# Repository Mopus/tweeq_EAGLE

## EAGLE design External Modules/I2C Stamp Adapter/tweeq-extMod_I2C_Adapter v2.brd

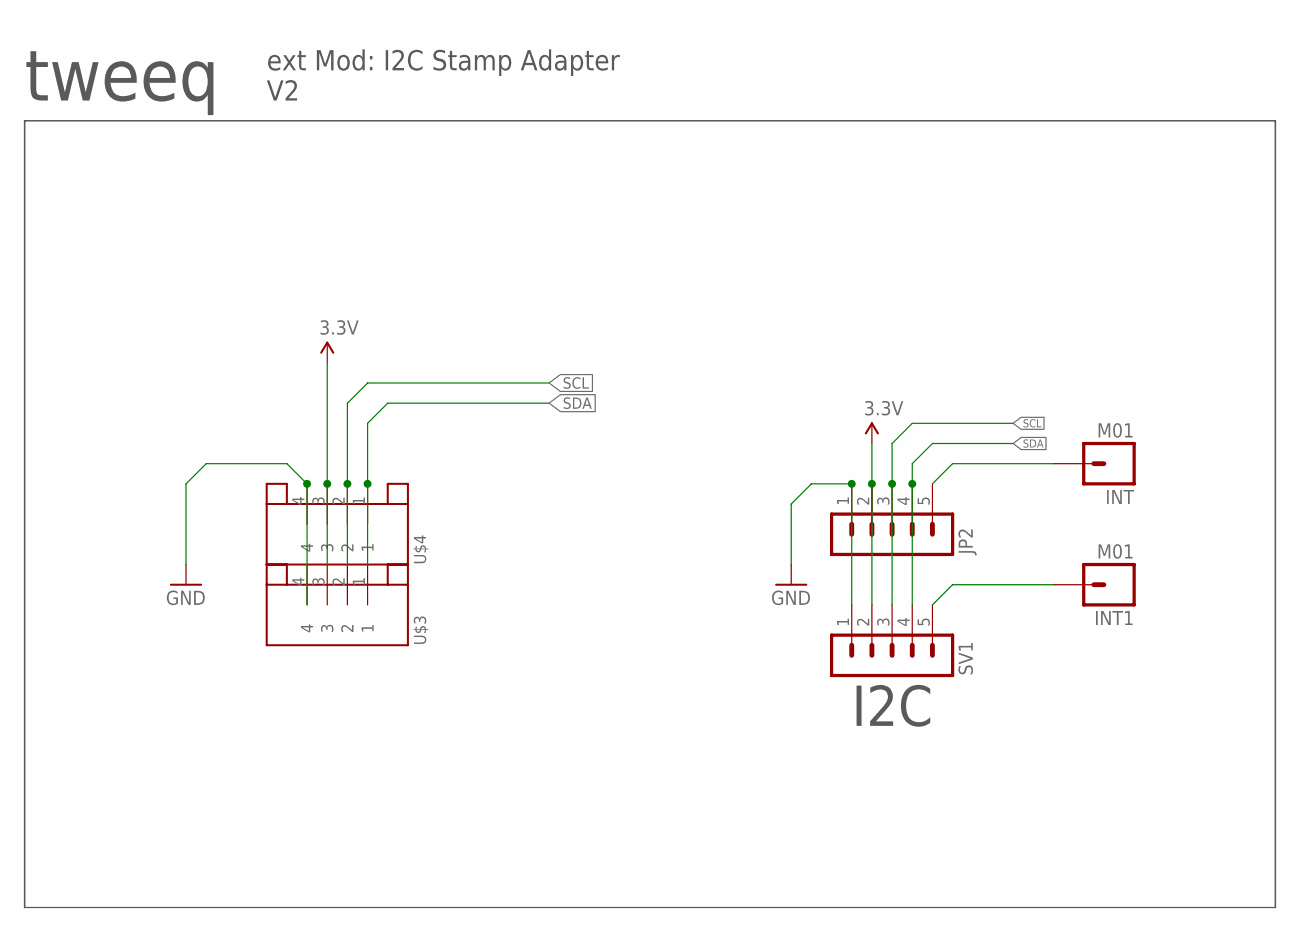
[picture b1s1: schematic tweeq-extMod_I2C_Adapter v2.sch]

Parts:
INT, INT1: M01; AISCUBE_1X01_TIGHTFITVIA
JP2: M05-11.5MM-SMT; 1X05-1.5MM-SMT
SV1: M05-11.5MM-SMT; 1X05-1.5MM-SMT
U$3, U$4: JST-4PINSH; SH1.0-4PIN

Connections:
3.3V: JP2.2, SV1.2, U$3.3, U$4.3
GND: JP2.1, SV1.1, U$4.4
INT: INT.P$1, JP2.5
unnamed: INT1.P$1, SV1.5
SCL: JP2.3, SV1.3, U$3.2, U$4.2
SDA: JP2.4, SV1.4, U$3.1, U$4.1

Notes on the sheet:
tweeq
ext Mod: I2C Stamp Adapter V2
I2C

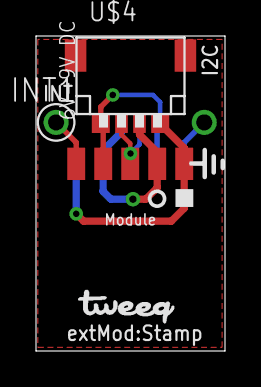
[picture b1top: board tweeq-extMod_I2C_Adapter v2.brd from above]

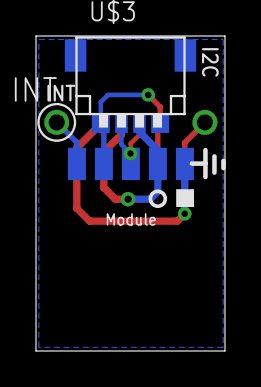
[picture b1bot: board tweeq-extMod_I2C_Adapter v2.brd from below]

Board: 2 copper layers, 10.5 x 17.5 mm, 7 parts (3 on the bottom side), 6 nets.

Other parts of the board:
U$1: TWEEQ-LOGO-S

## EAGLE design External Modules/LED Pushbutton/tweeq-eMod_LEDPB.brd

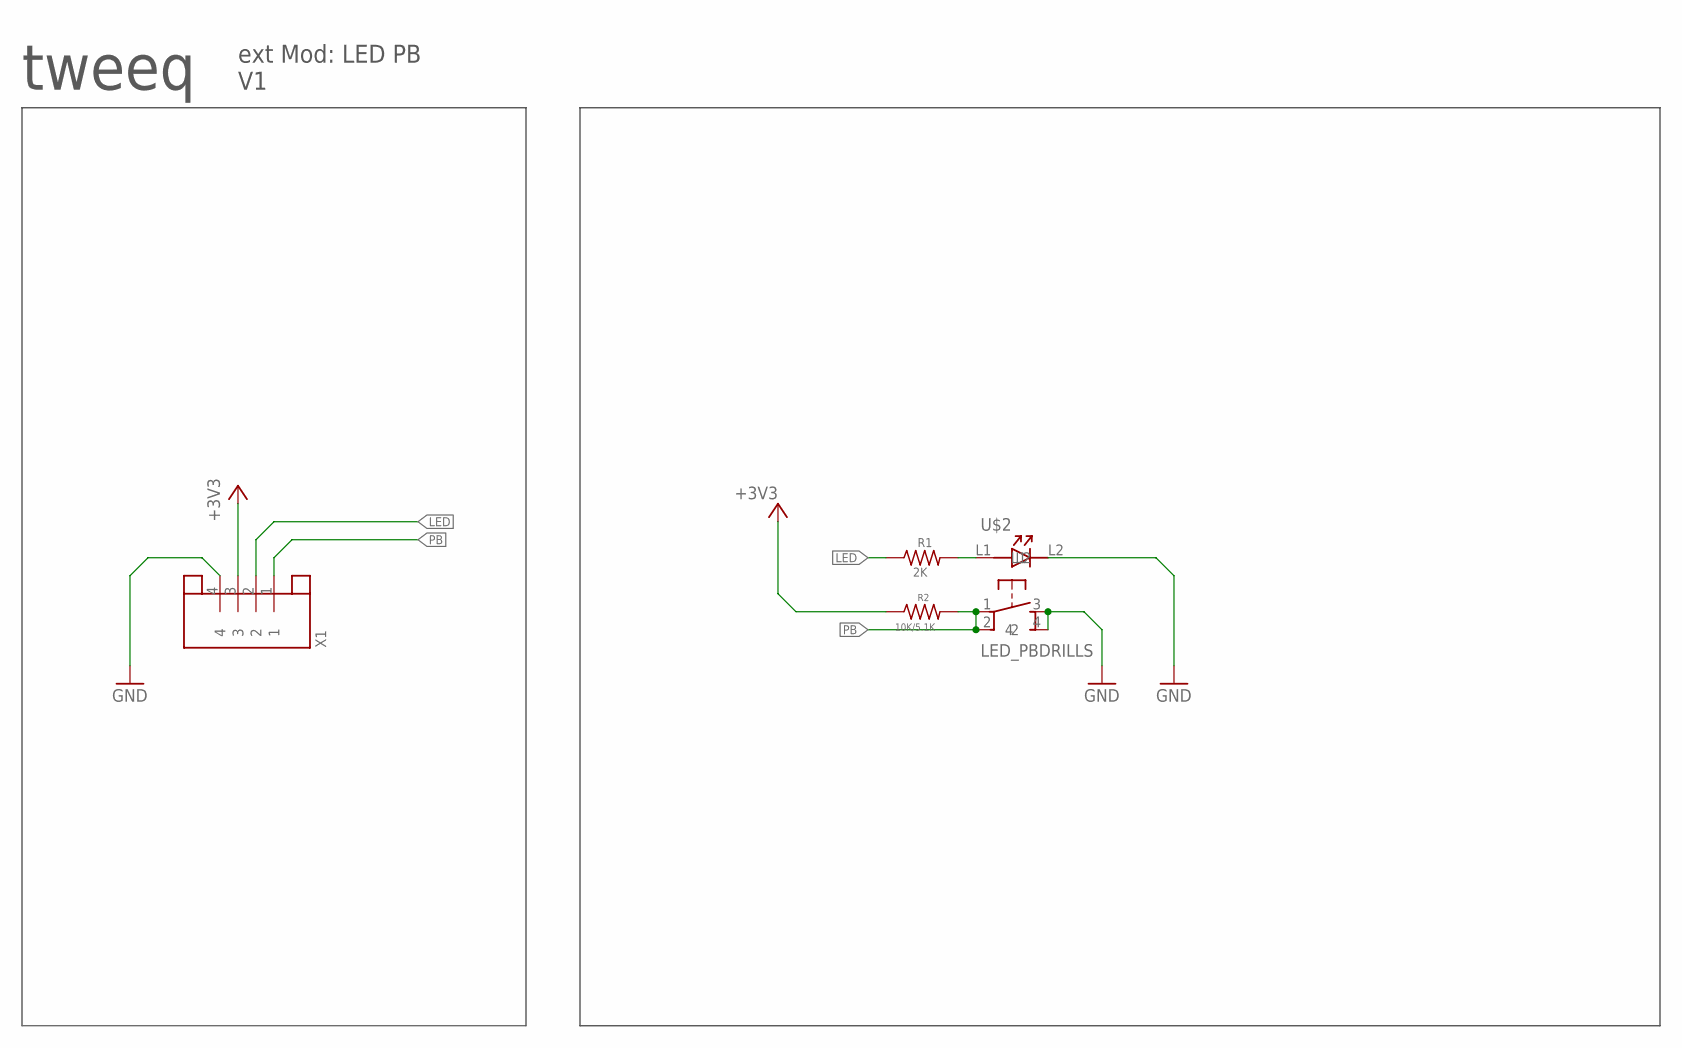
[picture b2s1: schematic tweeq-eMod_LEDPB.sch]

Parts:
R1: 2K; R0603
R2: 10K/5.1K; R0603
U$2: LED_PBDRILLS; LED_PB_12X12_SMD_HOLES
X1: JST-4PINSH; SH1.0-4PIN

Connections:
+3V3: R2.1, X1.3
GND: U$2.3, U$2.4, U$2.L2, X1.4
LED: R1.1, X1.2
unnamed: R1.2, U$2.L1
PB: R2.2, U$2.1, U$2.2, X1.1

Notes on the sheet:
tweeq
ext Mod: LED PB V1

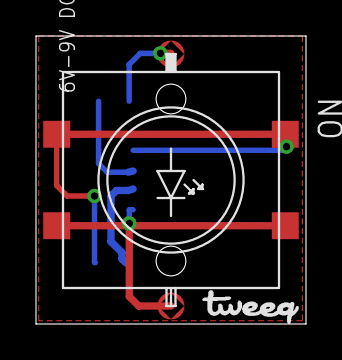
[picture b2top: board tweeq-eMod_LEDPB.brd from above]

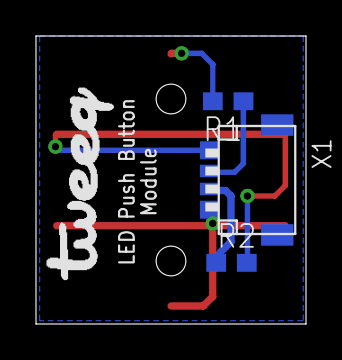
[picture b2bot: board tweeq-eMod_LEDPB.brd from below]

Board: 2 copper layers, 15.0 x 16.0 mm, 6 parts (4 on the bottom side), 5 nets.

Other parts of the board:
U$4: TWEEQ-LOGO-S
U$5: TWEEQ-LOGO-L

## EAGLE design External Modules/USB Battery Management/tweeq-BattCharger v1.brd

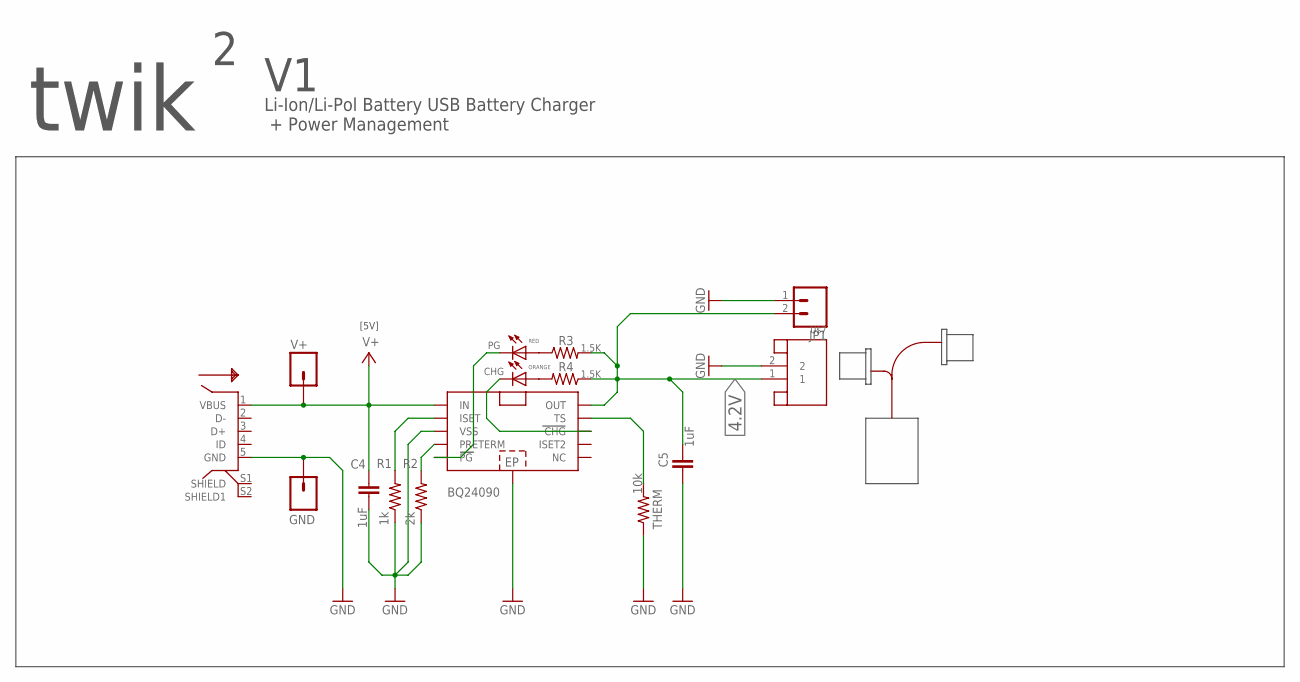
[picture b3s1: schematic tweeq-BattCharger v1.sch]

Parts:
BQ24090: BQ2409X-DGQ; MSOP10_POWERPAD
C4, C5: 1uF; C0603K
CHG: ORANGE; CHIP-LED0603
GND: M01SQ_NS; 1X01_SQ
JP1: M022.54-POL-TH; 1X02_2.54POL_TH
PG: RED; CHIP-LED0603
R1: 1k; R0402
R2: 2k; R0402
R3, R4: 1.5K; R0402
THERM: 10k; R0402
U$2: USB/MICRO-5PF-B; MICRO_USB_5PF_B
U$7: JST-2PINSH; SH1.0-2PIN
V+: M01/R_NS; 1X01NS

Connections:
4.2V: BQ24090.10 (OUT), C5.2, JP1.2, R3.2, R4.1, U$7.1
GND: BQ24090.3 (VSS), BQ24090.EP, C4.2, C5.1, GND.1, JP1.1, R1.1, R2.1, THERM.1, U$2.5 (GND), U$7.2
unnamed: BQ24090.2 (ISET), R1.2
unnamed: BQ24090.5 (PG), PG.C
unnamed: BQ24090.4 (PRETERM), R2.2
unnamed: PG.A, R3.1
unnamed: BQ24090.9 (TS), THERM.2
unnamed: BQ24090.8 (CHG), CHG.C
unnamed: CHG.A, R4.2
V+: BQ24090.1 (IN), C4.1, U$2.1 (VBUS), V+.1

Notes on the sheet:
[5V]
twik
Li-Ion/Li-Pol Battery USB Battery Charger + Power Management

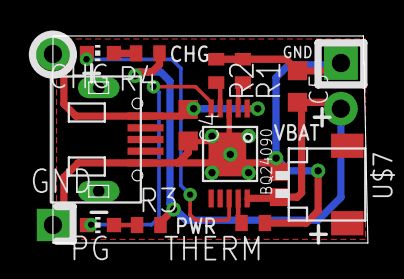
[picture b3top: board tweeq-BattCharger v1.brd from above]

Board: 2 copper layers, 17.5 x 11.5 mm, 16 parts (1 on the bottom side), 10 nets.

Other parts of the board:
U$1: TWEEQ-LOGO-M

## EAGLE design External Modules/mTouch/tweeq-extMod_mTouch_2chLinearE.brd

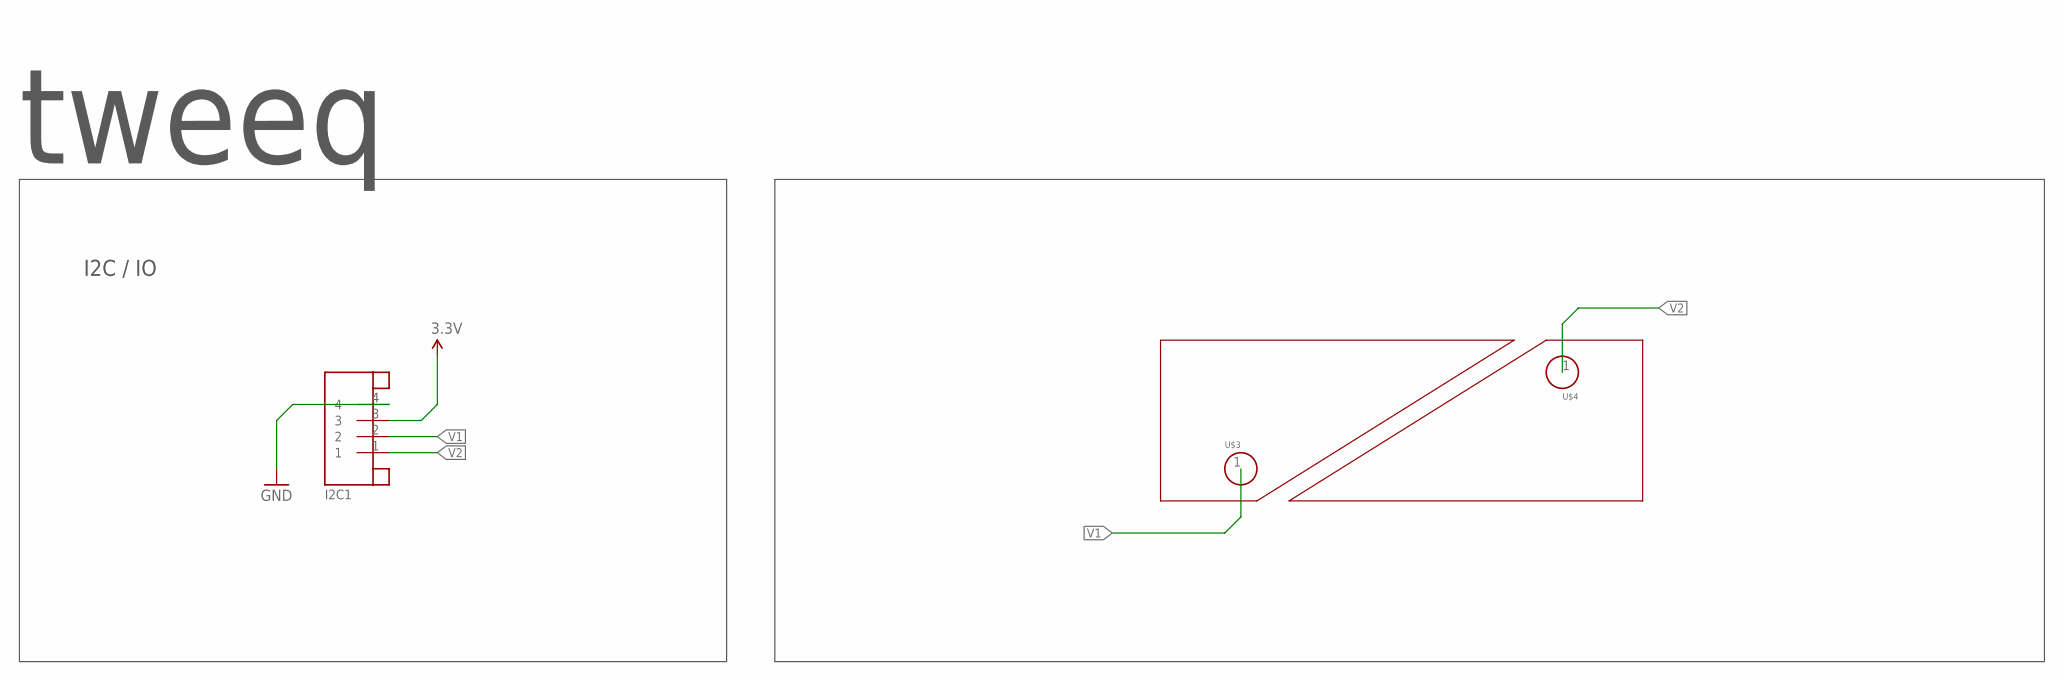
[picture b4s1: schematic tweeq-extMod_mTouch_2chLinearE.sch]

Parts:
I2C1: JST-4PINSH; SH1.0-4PIN
U$3, U$4: MTOUCH_VIA

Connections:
3.3V: I2C1.3
GND: I2C1.4
V1: I2C1.2, U$3.1
V2: I2C1.1, U$4.1

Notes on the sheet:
tweeq
I2C / IO

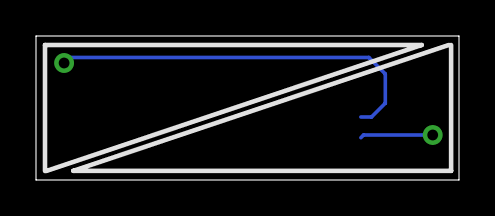
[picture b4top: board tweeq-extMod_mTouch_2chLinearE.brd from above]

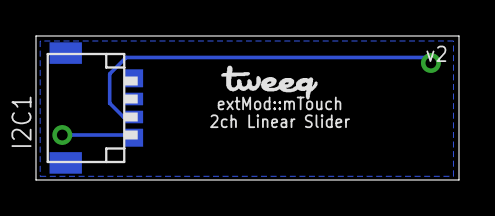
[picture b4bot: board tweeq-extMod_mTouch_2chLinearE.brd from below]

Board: 2 copper layers, 23.5 x 8.0 mm, 4 parts (2 on the bottom side), 2 nets.

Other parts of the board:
U$1: TWEEQ-LOGO-S

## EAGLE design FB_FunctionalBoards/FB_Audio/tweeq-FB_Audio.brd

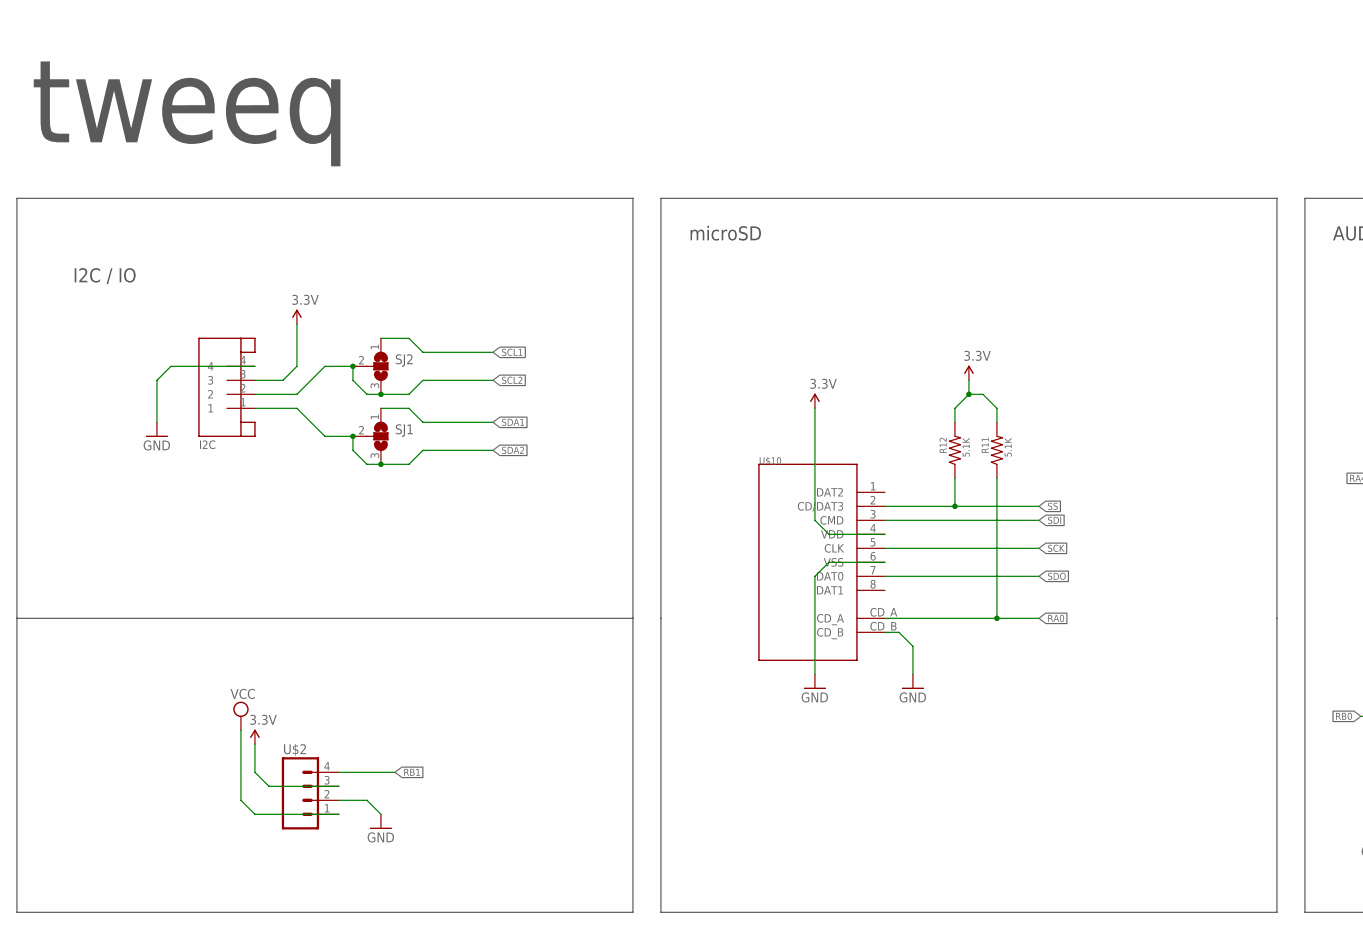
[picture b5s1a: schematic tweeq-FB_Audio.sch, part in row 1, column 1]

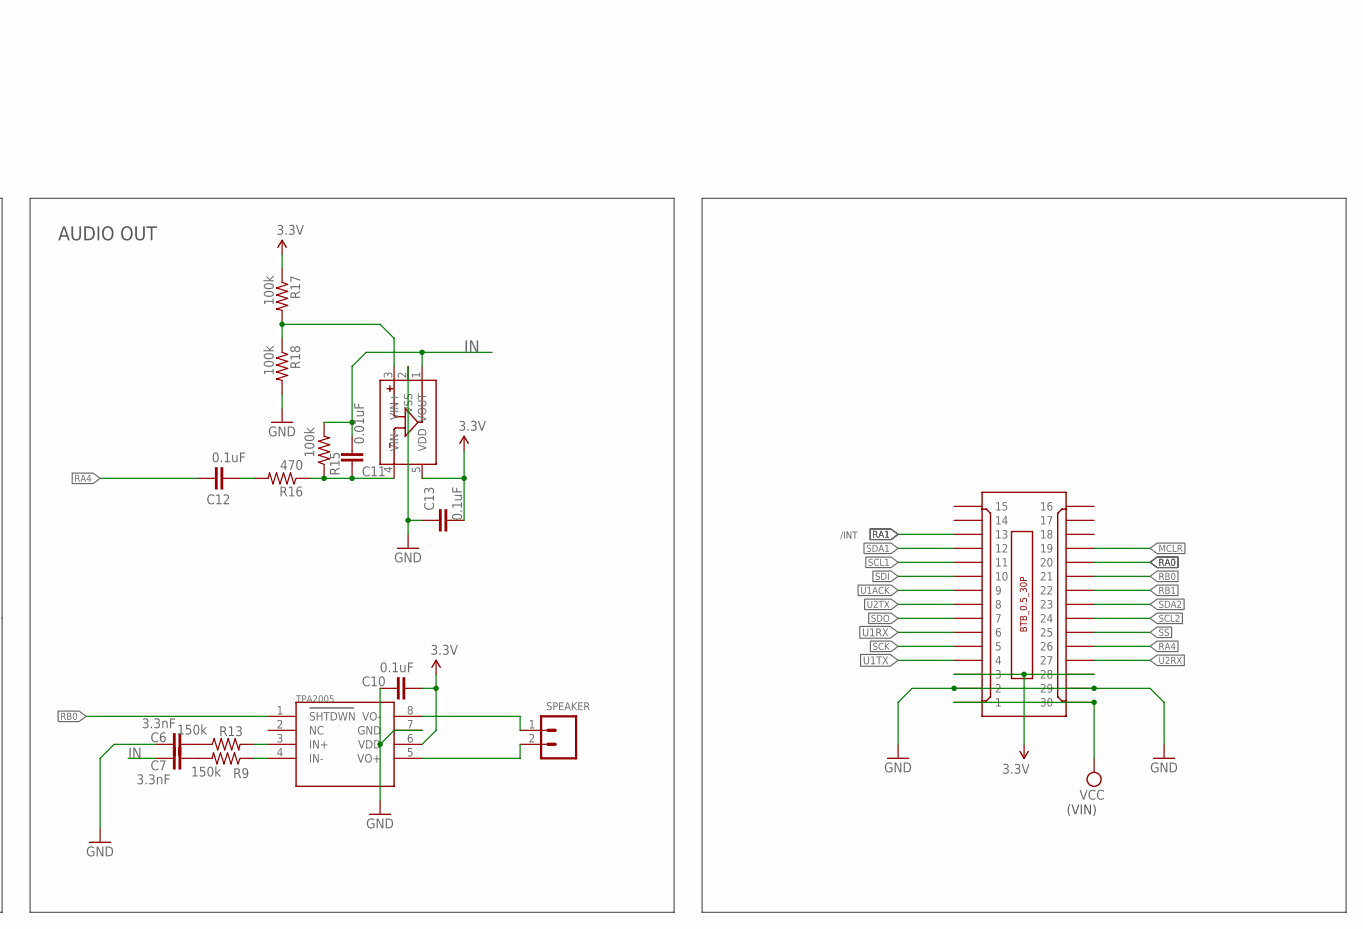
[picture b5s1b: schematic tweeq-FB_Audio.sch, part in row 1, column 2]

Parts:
C6, C7: 3.3nF; C0402
C10, C12, C13: 0.1uF; C0402
C11: 0.01uF; C0402
I2C: JST-4PINSH; SH1.0-4PIN
MCP6001/OT: MCP6001/OT; SOT23-5
R9, R13: 150k; R0402
R11, R12: 5.1K; R0402
R15, R17, R18: 100k; R0402
R16: 470; 0402-RES
SJ1, SJ2: JUMPER_SJ2WS; JUMPER_SJ_S
SPEAKER: LOUDSPEAKER; 1X02
TPA2005: TPA2005; MSOP8
U$1: BTB_CONN_30P/F; BTB0.5-30F-3.0G
U$2: M04; 1X04_PAD
U$10: MICROSD_DM3D; DM3D-SF

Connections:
3.3V: C10.2, C13.2, I2C.3, MCP6001/OT.5 (VDD), R11.2, R12.2, R17.1, TPA2005.6 (VDD), U$1.3, U$1.28, U$2.3, U$10.4 (VDD)
GND: C6.1, C10.1, C13.1, I2C.4, MCP6001/OT.2 (VSS), R18.2, TPA2005.7 (GND), U$1.2, U$1.29, U$2.2, U$10.6 (VSS), U$10.CD_B
IN: C7.2, C11.2, MCP6001/OT.1 (VOUT), R15.2
MCLR: U$1.19
unnamed: R9.1, TPA2005.4 (IN-)
unnamed: C7.1, R9.2
unnamed: R13.2, TPA2005.3 (IN+)
unnamed: C6.2, R13.1
unnamed: SPEAKER.1, TPA2005.8 (VO-)
unnamed: SPEAKER.2, TPA2005.5 (VO+)
unnamed: C12.2, R16.2
unnamed: C11.1, MCP6001/OT.4 (VIN-), R15.1, R16.1
unnamed: MCP6001/OT.3 (VIN+), R17.2, R18.1
RA0: R11.1, U$1.20, U$10.CD_A
RA1: U$1.13
RA4: C12.1, U$1.26
RB0: TPA2005.1 (SHTDWN), U$1.21
RB1: U$1.22, U$2.4
SCK: U$1.5, U$10.5 (CLK)
SCL1: SJ2.1, U$1.11
SCL2: I2C.2, SJ2.2, SJ2.3, U$1.24
SDA1: SJ1.1, U$1.12
SDA2: I2C.1, SJ1.2, SJ1.3, U$1.23
SDI: U$1.10, U$10.3 (CMD)
SDO: U$1.7, U$10.7 (DAT0)
SS: R12.1, U$1.25, U$10.2 (CD/DAT3)
U1ACK: U$1.9
U1RX: U$1.6
U1TX: U$1.4
U2RX: U$1.27
U2TX: U$1.8
VCC: U$1.1, U$1.30, U$2.1

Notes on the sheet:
AUDIO OUT
(VIN)
tweeq
microSD
I2C / IO
/INT

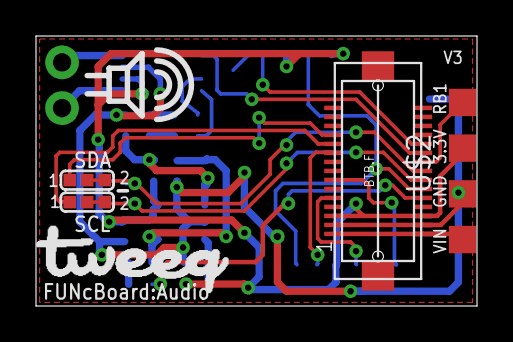
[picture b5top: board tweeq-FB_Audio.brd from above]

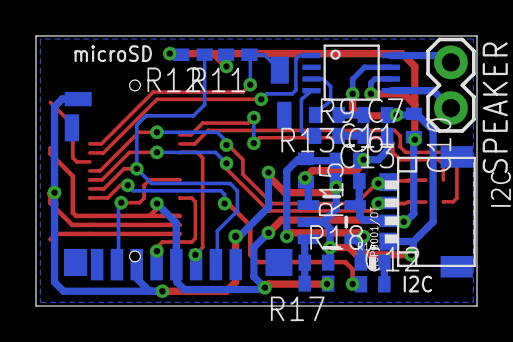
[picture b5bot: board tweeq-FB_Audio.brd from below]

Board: 2 copper layers, 24.5 x 15.0 mm, 24 parts (19 on the bottom side), 25 nets.

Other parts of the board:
U$4: TWEEQ-LOGO-L

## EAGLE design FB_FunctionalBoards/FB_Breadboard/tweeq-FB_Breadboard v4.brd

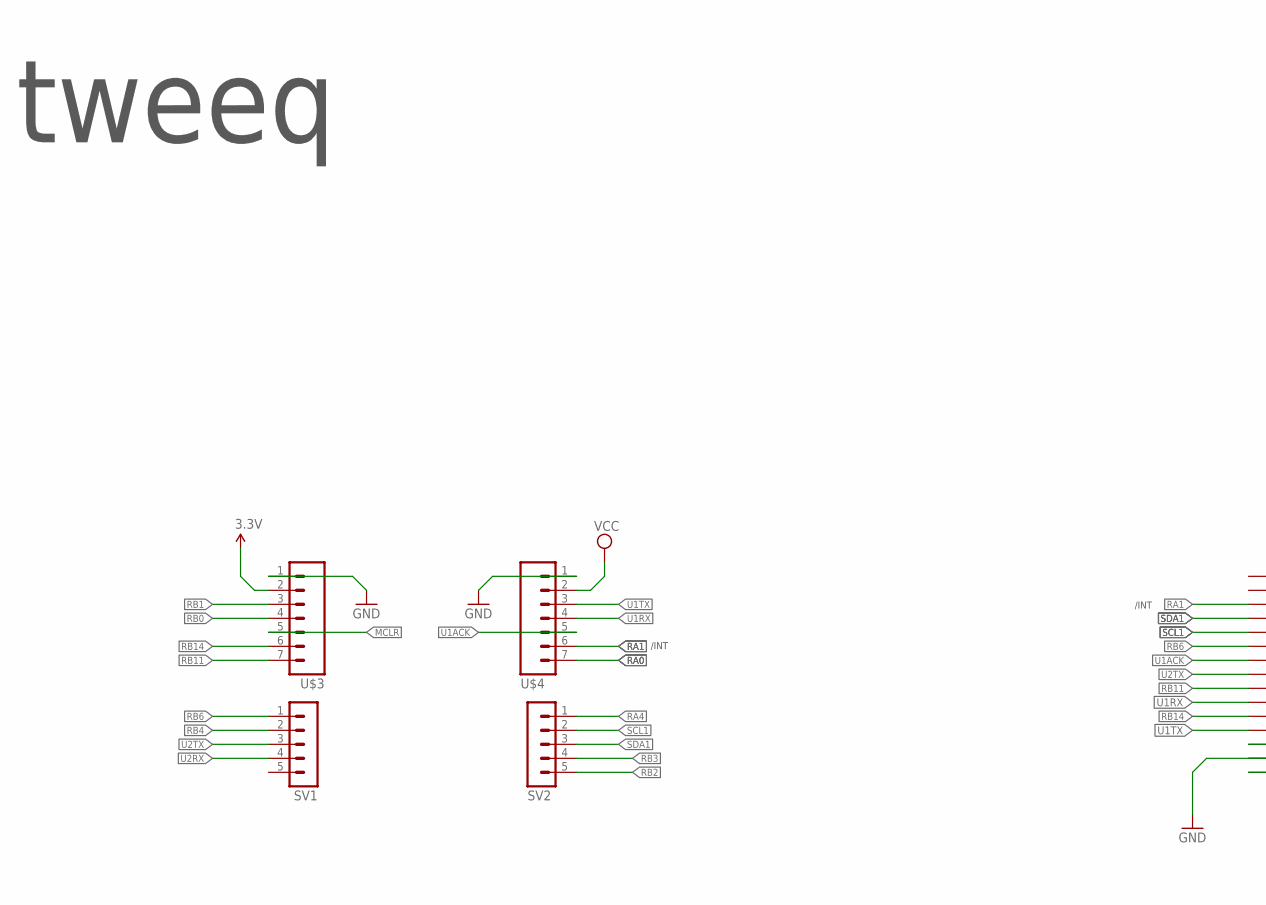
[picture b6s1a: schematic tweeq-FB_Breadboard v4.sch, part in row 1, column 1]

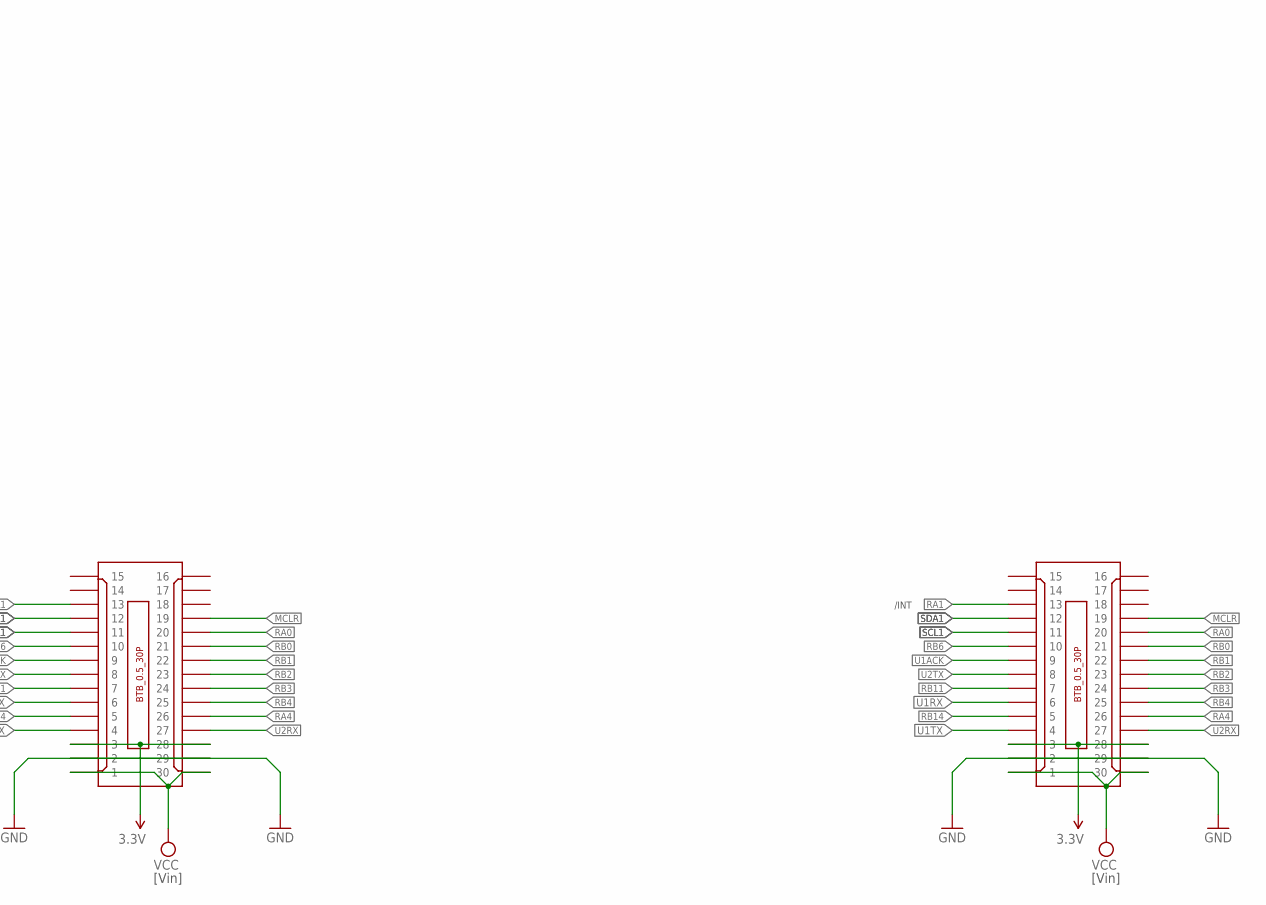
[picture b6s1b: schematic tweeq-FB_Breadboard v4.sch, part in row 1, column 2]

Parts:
SV1, SV2: M05-1NOSILK; 1X05_NOSILK
U$1: BTB_CONN_30P/M; BTB0.5-30M-3.0G
U$2: BTB_CONN_30P/F; BTB0.5-30F-3.0G
U$3, U$4: M07NOSILK; 1X07_NOSILK

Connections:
3.3V: U$1.3, U$1.28, U$2.3, U$2.28, U$3.2
GND: U$1.2, U$1.29, U$2.2, U$2.29, U$3.1, U$4.1
MCLR: U$1.19, U$2.19, U$3.5
RA0: U$1.20, U$2.20, U$4.7
RA1: U$1.13, U$2.13, U$4.6
RA4: SV2.1, U$1.26, U$2.26
RB0: U$1.21, U$2.21, U$3.4
RB1: U$1.22, U$2.22, U$3.3
RB2: SV2.5, U$1.23, U$2.23
RB3: SV2.4, U$1.24, U$2.24
RB4: SV1.2, U$1.25, U$2.25
RB6: SV1.1, U$1.10, U$2.10
RB11: U$1.7, U$2.7, U$3.7
RB14: U$1.5, U$2.5, U$3.6
SCL1: SV2.2, U$1.11, U$2.11
SDA1: SV2.3, U$1.12, U$2.12
U1ACK: U$1.9, U$2.9, U$4.5
U1RX: U$1.6, U$2.6, U$4.4
U1TX: U$1.4, U$2.4, U$4.3
U2RX: SV1.4, U$1.27, U$2.27
U2TX: SV1.3, U$1.8, U$2.8
VCC: U$1.1, U$1.30, U$2.1, U$2.30, U$4.2

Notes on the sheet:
[Vin]
/INT
tweeq

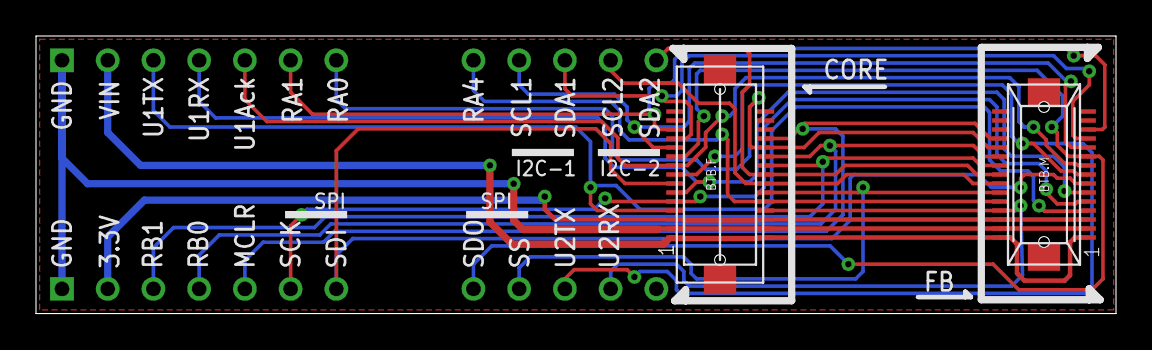
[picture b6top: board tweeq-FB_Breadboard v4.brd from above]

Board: 2 copper layers, 60.0 x 15.4 mm, 7 parts (1 on the bottom side), 22 nets.

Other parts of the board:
U$5: TWEEQ-LOGO-L

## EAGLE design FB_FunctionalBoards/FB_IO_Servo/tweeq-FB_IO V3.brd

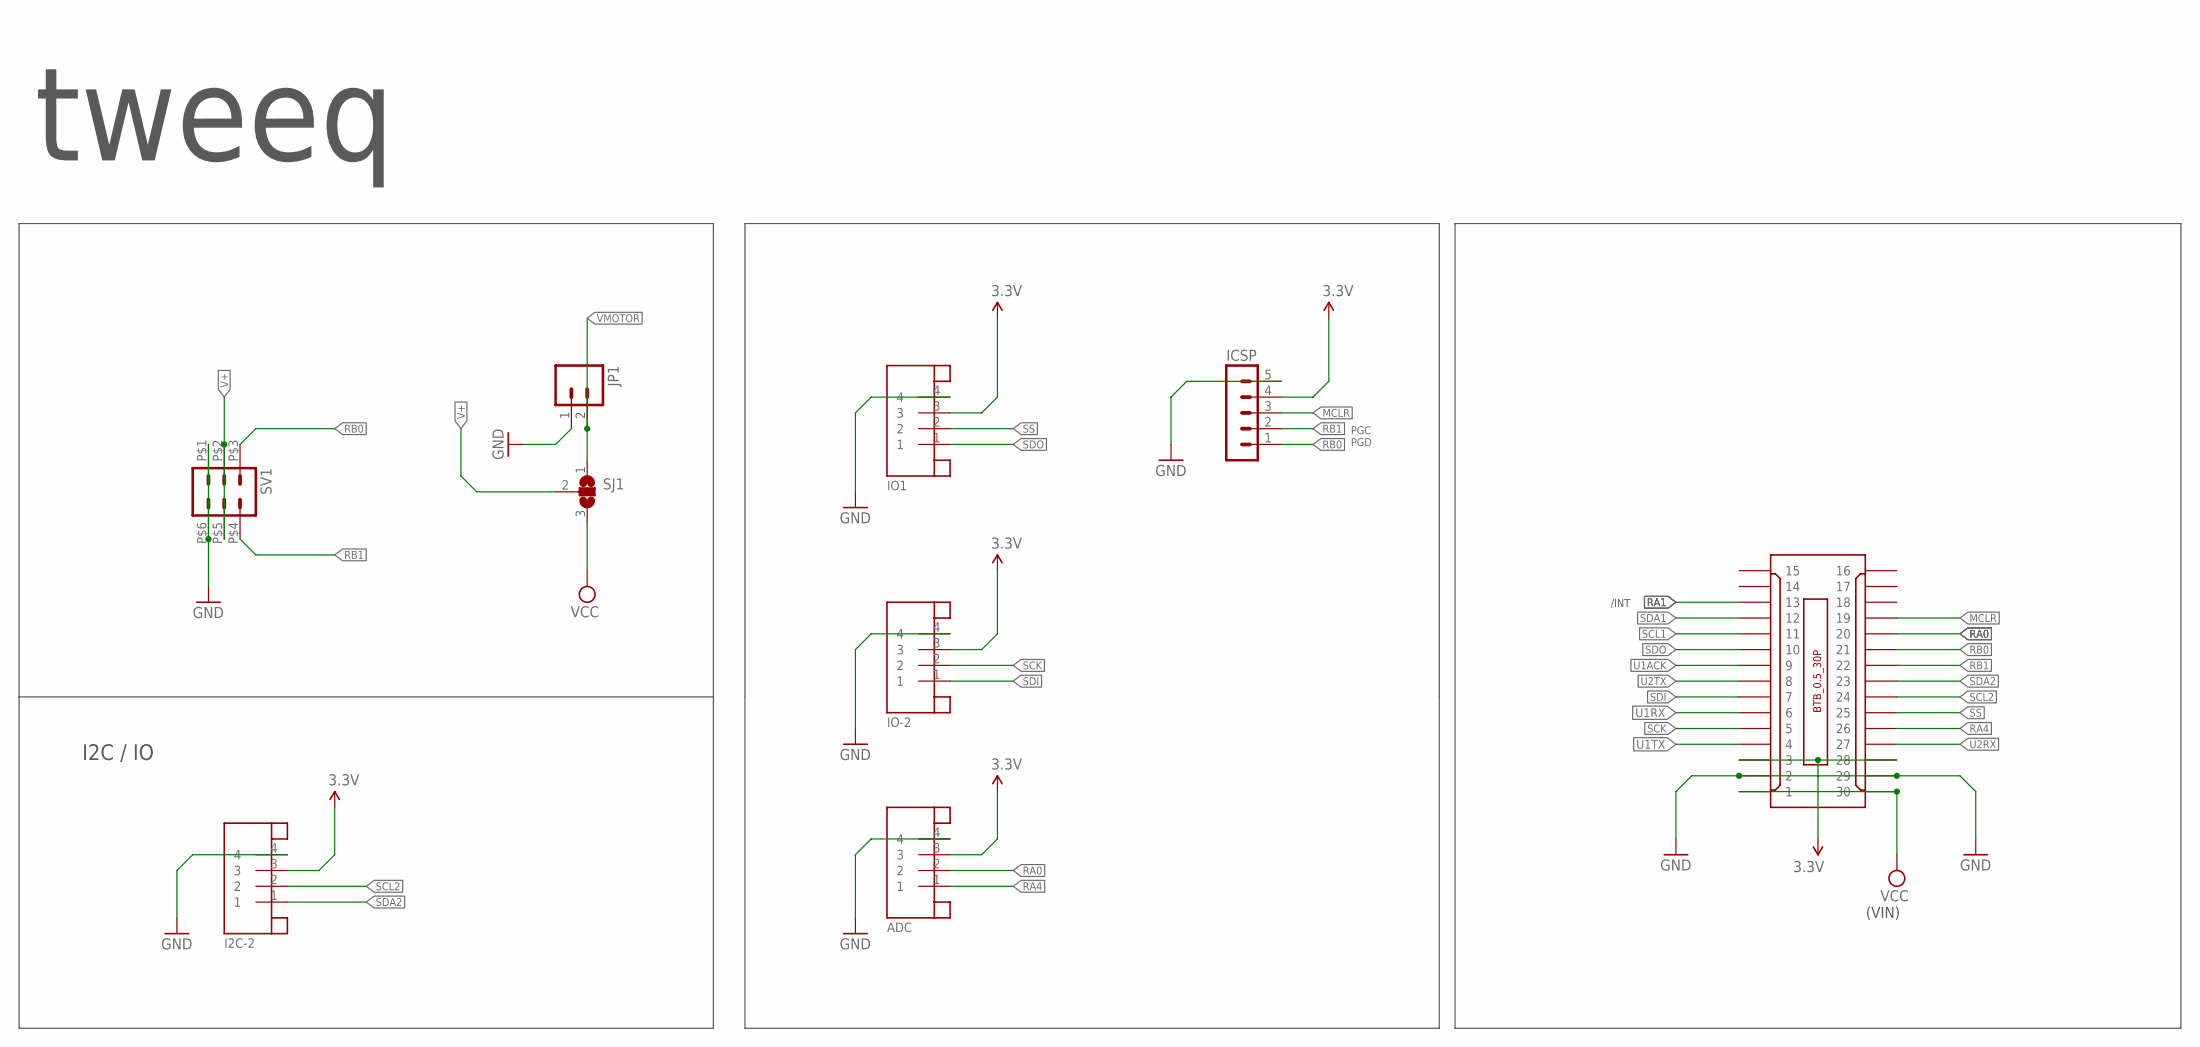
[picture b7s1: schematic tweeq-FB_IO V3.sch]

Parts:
ADC: JST-4PINSH; SH1.0-4PIN
I2C-2: JST-4PINSH; SH1.0-4PIN
ICSP: M05-1NOSILK; 1X05_NOSILK
IO1: JST-4PINSH; SH1.0-4PIN
IO-2: JST-4PINSH; SH1.0-4PIN
JP1: M022.54-POL-TH; 1X02_2.54POL_TH
SJ1: JUMPER_SJ2W; JUMPER_SJ_2
SV1: M03-2EDGE_PAD; 2X03_EDGEPAD
U$1: BTB_CONN_30P/F; BTB0.5-30F-3.0G

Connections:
3.3V: ADC.3, I2C-2.3, ICSP.4, IO1.3, IO-2.3, U$1.3, U$1.28
GND: ADC.4, I2C-2.4, ICSP.5, IO1.4, IO-2.4, JP1.1, SV1.P$1 (1), SV1.P$6 (6), U$1.2, U$1.29
MCLR: ICSP.3, U$1.19
RA0: ADC.2, U$1.20
RA1: U$1.13
RA4: ADC.1, U$1.26
RB0: ICSP.1, SV1.P$3 (3), U$1.21
RB1: ICSP.2, SV1.P$4 (4), U$1.22
SCK: IO-2.2, U$1.5
SCL1: U$1.11
SCL2: I2C-2.2, U$1.24
SDA1: U$1.12
SDA2: I2C-2.1, U$1.23
SDI: IO-2.1, U$1.7
SDO: IO1.1, U$1.10
SS: IO1.2, U$1.25
U1ACK: U$1.9
U1RX: U$1.6
U1TX: U$1.4
U2RX: U$1.27
U2TX: U$1.8
V+: SJ1.2, SV1.P$2 (2), SV1.P$5 (5)
VCC: SJ1.3, U$1.1, U$1.30
VMOTOR: JP1.2, SJ1.1

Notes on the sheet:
(VIN)
tweeq
I2C / IO
/INT
PGC PGD
